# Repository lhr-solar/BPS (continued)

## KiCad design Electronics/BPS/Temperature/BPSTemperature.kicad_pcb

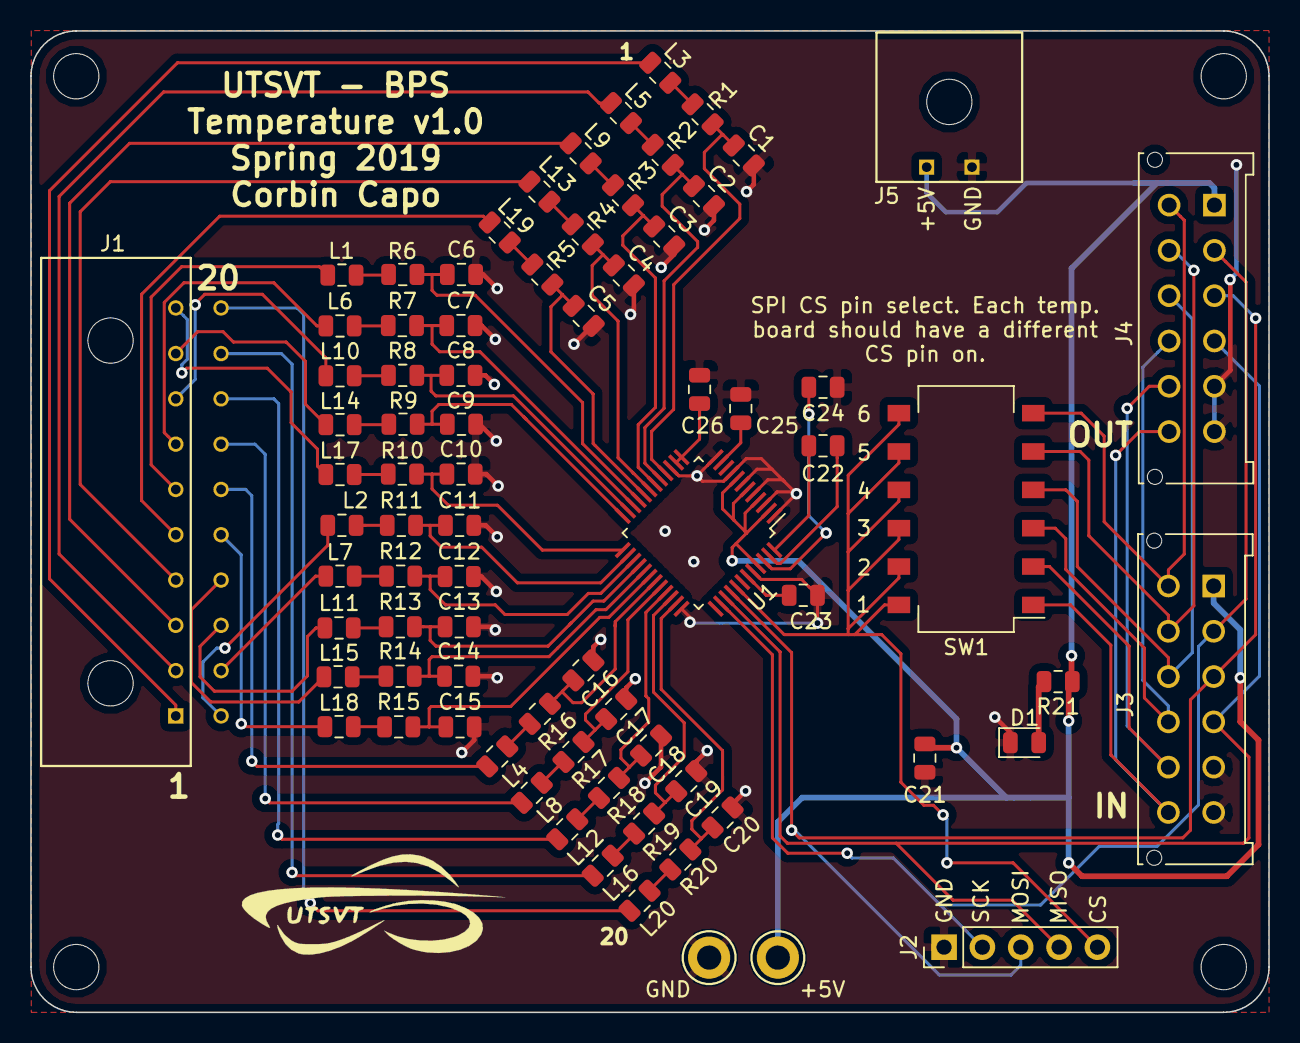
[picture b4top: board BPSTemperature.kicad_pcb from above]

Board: 2 copper layers, 82.0 x 65.0 mm, 81 parts (0 on the bottom side), 79 nets.

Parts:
+5V: TestPoint; TestPoint_Keystone_5005-5009_Compact
C1, C2, C3, C4, C5, C6, C7, C8, C9, C10, C11, C12, C13, C14, C15, C16, C17, C18, C19, C20, C25, C26: 1uF; C_0805_2012Metric
C21: 0.1uF; C_0805_2012Metric
C22, C23, C24: 10uF; C_0805_2012Metric
D1: LED; LED_0805_2012Metric
GND: TestPoint; TestPoint_Keystone_5005-5009_Compact
J1: Conn_02x10_Counter_Clockwise; 02x10_Microfit_3.0_horizontal
J2: Logic Analyzer; PinHeader_1x05_P2.54mm_Vertical
J3, J4: Conn_02x06_Counter_Clockwise; Molex_MicroFit3.0_2x6xP3.00mm_PolarizingPeg_Vertical
J5: Conn_01x02; 43650-0202_01x02_Microfit 3.0_horizontal
L1, L2, L3, L4, L5, L6, L7, L8, L9, L10, L11, L12, L13, L14, L15, L16, L17, L18, L19, L20: Ferrite_Bead; L_0805_2012Metric
MH1, MH2, MH3, MH4: MountingHole; MountingHole_3mm
R1, R2, R3, R4, R5, R6, R7, R8, R9, R10, R11, R12, R13, R14, R15, R16, R17, R18, R19, R20: 1k; R_0805_2012Metric
R21: 1.55k; R_0805_2012Metric
SW1: SW_DIP_x06; SW_DIP_SPSTx06_Slide_Omron_A6S-610x_W8.9mm_P2.54mm
U1: LTC2983; LQFP-48_7x7mm_P0.5mm

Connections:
+5V: +5V.1, C21.2, J3.1, J4.1, J5.1, R21.1, U1.2, U1.4, U1.6, U1.8, U1.45
/CH1_LPF: J1.1, L3.2
/CH2_LPF: J1.2, L5.2
/CH3_LPF: J1.3, L9.2
/CH4_LPF: J1.4, L13.2
/CH5_LPF: J1.5, L19.2
/CH6_LPF: J1.6, L1.1
/CH7_LPF: J1.7, L6.1
/CH8_LPF: J1.8, L10.1
/CH9_LPF: J1.9, L14.1
/CH10_LPF: J1.10, L17.2
/CH11_LPF: J1.11, L2.1
/CH12_LPF: J1.12, L7.1
/CH13_LPF: J1.13, L11.1
/CH14_LPF: J1.14, L15.1
/CH15_LPF: J1.15, L18.1
/CH16_LPF: J1.16, L4.1
/CH17_LPF: J1.17, L8.1
/CH18_LPF: J1.18, L12.1
/CH19_LPF: J1.19, L16.1
/CH20_LPF: J1.20, L20.1
/CS1: J3.12, J4.12, SW1.1
/CS1_OUT: J2.5, SW1.7, SW1.8, SW1.9, SW1.10, SW1.11, SW1.12, U1.41
/CS2: J3.11, J4.11, SW1.2
/CS3: J3.10, J4.10, SW1.3
/CS4: J3.9, J4.9, SW1.4
/CS5: J3.8, J4.8, SW1.5
/CS6: J3.7, J4.7, SW1.6
/MISO: J2.4, J3.4, J4.4, U1.39
/MOSI: J2.3, J3.3, J4.3, U1.40
/SCK: J2.2, J3.2, J4.2, U1.38
GND: C1.2, C2.2, C3.2, C4.2, C5.2, C6.2, C7.2, C8.2, C9.2, C10.2, C11.2, C12.2, C13.2, C14.2, C15.2, C16.2, C17.2, C18.2, C19.2, C20.2, C21.1, C23.2, C24.2, C25.2, C26.2, D1.1, GND.1, J2.1, J3.5, J3.6, J4.5, J4.6, J5.2, U1.1, U1.3, U1.5, U1.7, U1.9, U1.12, U1.15, U1.36, U1.44
unnamed: C1.1, R1.2, U1.16
unnamed: C2.1, R2.2, U1.17
unnamed: C3.1, R3.2, U1.18
unnamed: C4.1, R4.2, U1.19
unnamed: C5.1, R5.2, U1.20
unnamed: C6.1, R6.2, U1.21
unnamed: C7.1, R7.2, U1.22
unnamed: C8.1, R8.2, U1.23
unnamed: C9.1, R9.2, U1.24
unnamed: C10.1, R10.2, U1.25
unnamed: C11.1, R11.2, U1.26
unnamed: C12.1, R12.2, U1.27
unnamed: C13.1, R13.2, U1.28
unnamed: C14.1, R14.2, U1.29
unnamed: C15.1, R15.2, U1.30
unnamed: C16.1, R16.2, U1.31
unnamed: C17.1, R17.2, U1.32
unnamed: C18.1, R18.2, U1.33
unnamed: C19.1, R19.2, U1.34
unnamed: C20.1, R20.2, U1.35
unnamed: C22.1, U1.48
unnamed: C22.2, U1.47
unnamed: C23.1, U1.43
unnamed: C24.1, U1.46
unnamed: C25.1, U1.11
unnamed: C26.1, U1.13, U1.14
unnamed: D1.2, R21.2
unnamed: L1.2, R6.1
unnamed: L2.2, R11.1
unnamed: L3.1, R1.1
unnamed: L4.2, R16.1
unnamed: L5.1, R2.1
unnamed: L6.2, R7.1
unnamed: L7.2, R12.1
unnamed: L8.2, R17.1
unnamed: L9.1, R3.1
unnamed: L10.2, R8.1
unnamed: L11.2, R13.1
unnamed: L12.2, R18.1
unnamed: L13.1, R4.1
unnamed: L14.2, R9.1
unnamed: L15.2, R14.1
unnamed: L16.2, R19.1
unnamed: L17.1, R10.1
unnamed: L18.2, R15.1
unnamed: L19.1, R5.1
unnamed: L20.2, R20.1

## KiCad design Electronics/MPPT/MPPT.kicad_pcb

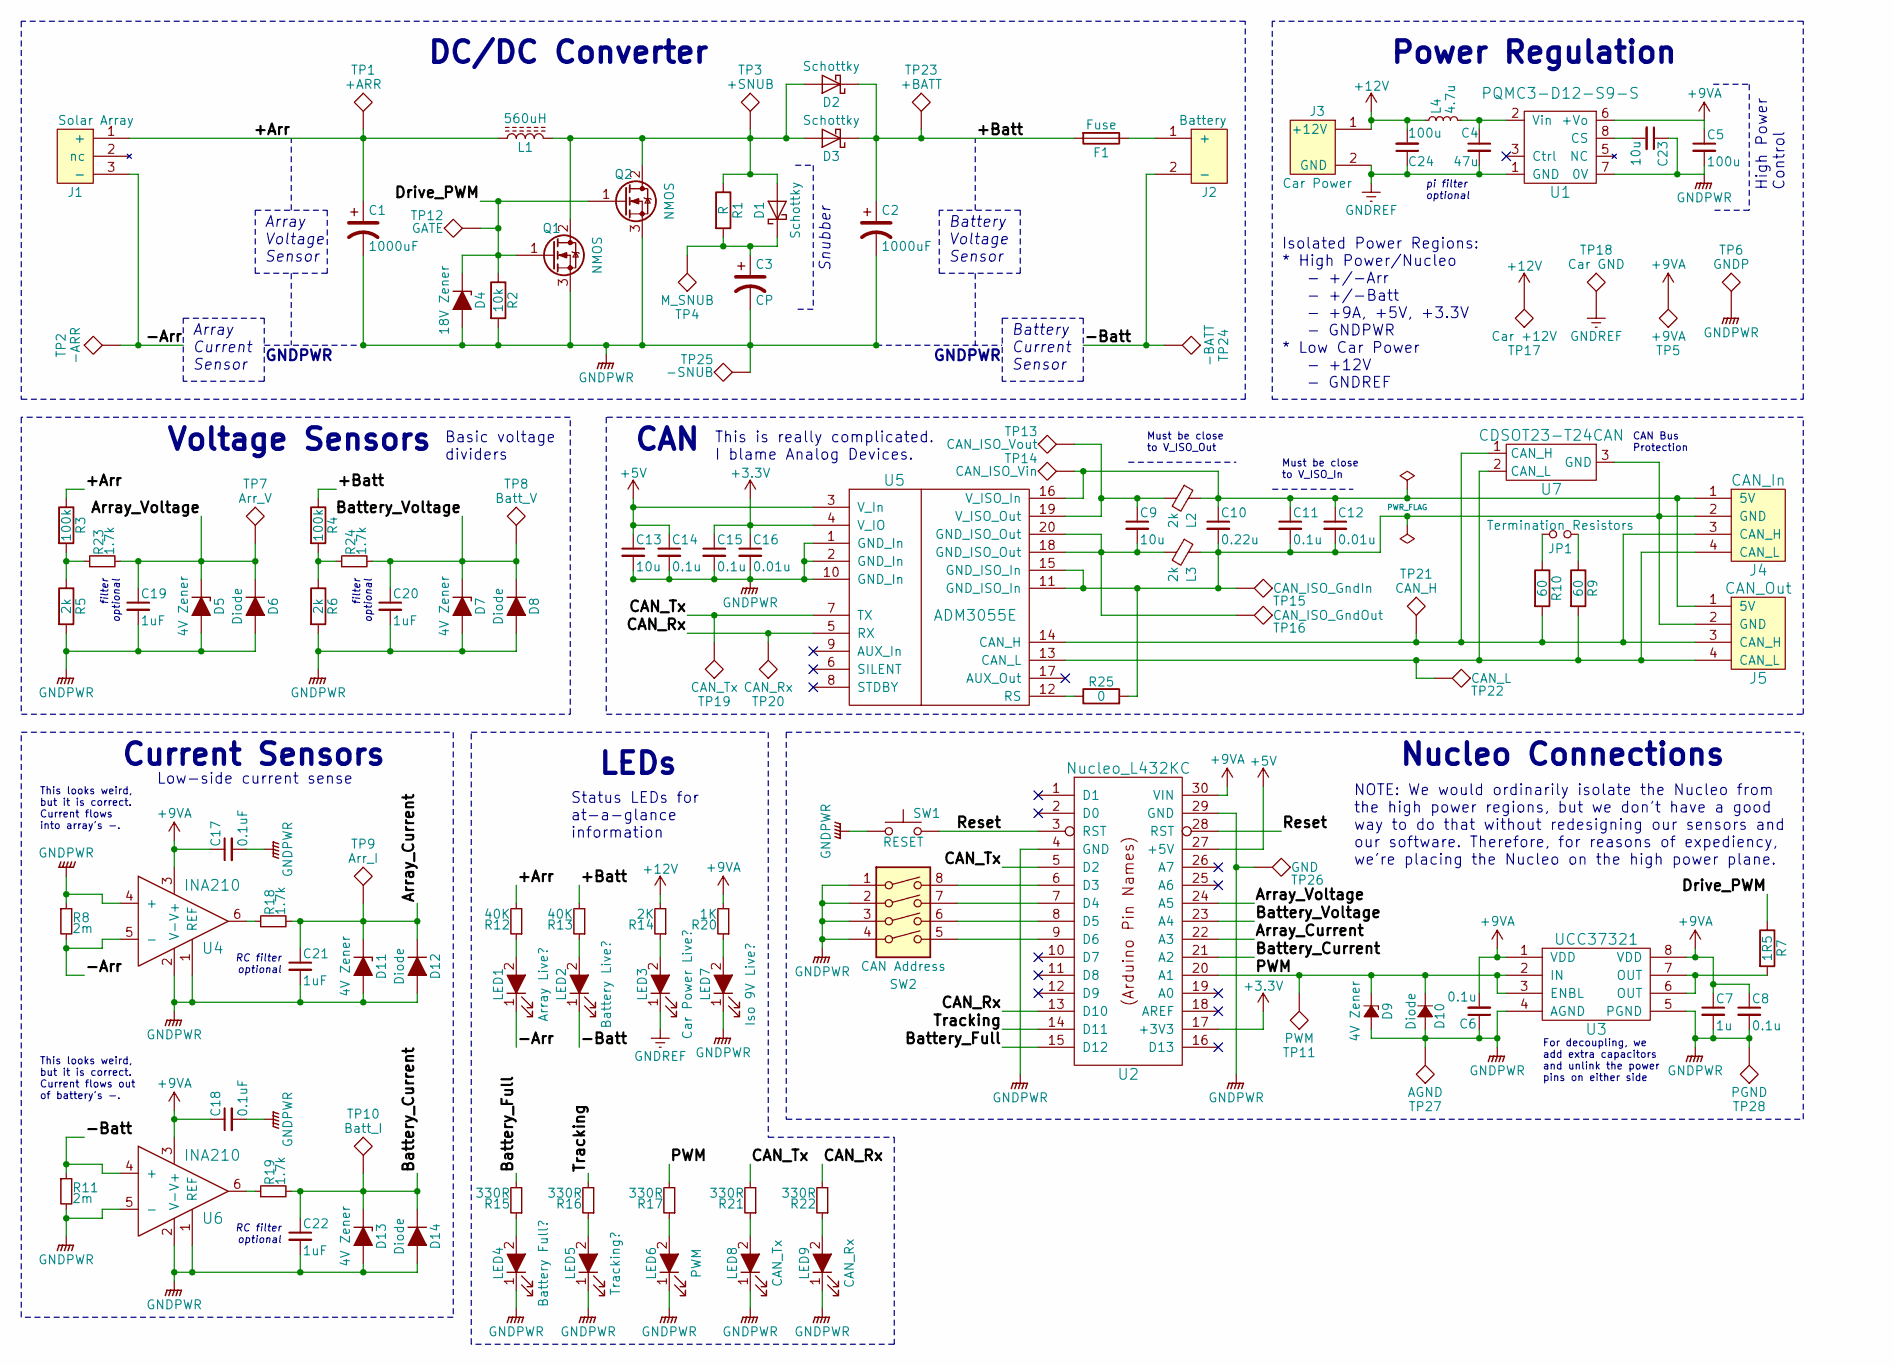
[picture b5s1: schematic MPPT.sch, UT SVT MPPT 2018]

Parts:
C1, C2: 1000uF; CP_Radial_D31mm_P9mm
C3: CP; C_Rect_L26.5mm_W17.0mm_P22.50mm_MKS4
C4: 47u; C_0805_HandSoldering
C5, C24: 100u; C_0805_HandSoldering
C6, C8, C11: 0.1u; C_0805_HandSoldering
C7: 1u; CP_Radial_D10.0mm_P5.00mm
C9, C23: 10u; C_0805_HandSoldering
C10: 0.22u; C_0805_HandSoldering
C12: 0.01u; C_0805_HandSoldering
C13: 10u; C_0805
C14, C15: 0.1u; C_0805
C16: 0.01u; C_0805
C17, C18: 0.1uF; C_0805_HandSoldering
C19, C20, C21, C22: 1uF; C_0805_HandSoldering
D1, D2, D3: Schottky; TO-220-2_Vertical
D4: 18V Zener; D_SMA_Handsoldering
D5, D7, D9, D11, D13: 4V Zener; D_SOD-123F
D6, D8, D10, D12, D14: Diode; D_SOD-123
F1: Fuse; LittelFuse_OMNIBLOK_520Series_PCB
J1: Solar Array; PhoenixContact_PowerCombicon5_GF_3x7.62mm
J2: Battery; PhoenixContact_PowerCombicon5_GF_2x7.62mm
J3: Car Power; Molex_MicroFit3.0_1x2xP3.00mm_PolarizingPeg_Vertical
J4: CAN_In; Molex_MicroFit3.0_1x4xP3.00mm_PolarizingPeg_Vertical
J5: CAN_Out; Molex_MicroFit3.0_1x4xP3.00mm_PolarizingPeg_Vertical
JP1: Termination Resistors; Pin_Header_Straight_1x02_Pitch2.54mm
L1: 560uH; L_Toroid_Vertical_L46.0mm_W19.1mm_P21.80mm_Bourns_5700
L2, L3: 2k; L_0805_HandSoldering
L4: 4.7u; L_0805_HandSoldering
LED1: Array Live?; LED_0805_HandSoldering
LED2: Battery Live?; LED_0805_HandSoldering
LED3: Car Power Live?; LED_0805_HandSoldering
LED4: Battery Full?; LED_0805_HandSoldering
LED5: Tracking?; LED_0805_HandSoldering
LED6: PWM; LED_0805_HandSoldering
LED7: Iso 9V Live?; LED_0805_HandSoldering
LED8: CAN_Tx; LED_0805_HandSoldering
LED9: CAN_Rx; LED_0805_HandSoldering
Q1, Q2: NMOS; TO-247_TO-3P_Vertical
R1: R; R_Axial_Power_L20.0mm_W6.4mm_P22.40mm
R2: 10k; R_1206_HandSoldering
R3, R4: 100k; R_1206_HandSoldering
R5, R6: 2k; R_1206_HandSoldering
R7: 1R5; R_1206_HandSoldering
R8, R11: 2m; R_2512_HandSoldering
R9, R10: 60; R_0805_HandSoldering
R12, R13: 40K; R_1206_HandSoldering
R14: 2K; R_0805_HandSoldering
R15, R16, R17, R21, R22: 330R; R_0805_HandSoldering
R18, R19, R23, R24: 1.7k; R_0805_HandSoldering
R20: 1K; R_0805_HandSoldering
R25: 0; R_0805_HandSoldering
SW1: RESET; SW_PUSH_6mm
SW2: CAN Address; SW_DIP_x4_W7.62mm_Slide_LowProfile
TP1: +ARR; Test_Point_Keystone_5005-5009_Compact
TP2: -ARR; Test_Point_Keystone_5005-5009_Compact
TP3: +SNUB; Test_Point_Keystone_5005-5009_Compact
TP4: M_SNUB; Test_Point_Keystone_5005-5009_Compact
TP5: +9VA; Test_Point_Keystone_5005-5009_Compact
TP6: GNDP; Test_Point_Keystone_5005-5009_Compact
TP7: Arr_V; Test_Point_Keystone_5005-5009_Compact
TP8: Batt_V; Test_Point_Keystone_5005-5009_Compact
TP9: Arr_I; Test_Point_Keystone_5005-5009_Compact
TP10: Batt_I; Test_Point_Keystone_5005-5009_Compact
TP11: PWM; Test_Point_Keystone_5005-5009_Compact
TP12: GATE; Test_Point_Keystone_5005-5009_Compact
TP13: CAN_ISO_Vout; Test_Point_Keystone_5005-5009_Compact
TP14: CAN_ISO_Vin; Test_Point_Keystone_5005-5009_Compact
TP15: CAN_ISO_GndIn; Test_Point_Keystone_5005-5009_Compact
TP16: CAN_ISO_GndOut; Test_Point_Keystone_5005-5009_Compact
TP17: Car +12V; Test_Point_Keystone_5005-5009_Compact
TP18: Car GND; Test_Point_Keystone_5005-5009_Compact
TP19: CAN_Tx; Test_Point_Keystone_5005-5009_Compact
TP20: CAN_Rx; Test_Point_Keystone_5005-5009_Compact
TP21: CAN_H; Test_Point_Keystone_5005-5009_Compact
TP22: CAN_L; Test_Point_Keystone_5005-5009_Compact
TP23: +BATT; Test_Point_Keystone_5005-5009_Compact
TP24: -BATT; Test_Point_Keystone_5005-5009_Compact
TP25: -SNUB; Test_Point_Keystone_5005-5009_Compact
TP26: GND; Test_Point_Keystone_5005-5009_Compact
TP27: AGND; Test_Point_Keystone_5005-5009_Compact
TP28: PGND; Test_Point_Keystone_5005-5009_Compact
U1: PQMC3-D12-S9-S; CUI_PQMC3-S
U2: Nucleo_L432KC; NucleoL432KC
U3: UCC37321; SOIC-8_4.00x5.00mm_Pitch1.27mm
U4, U6: INA210; SOIC-6_1.40x2.15mm_Pitch0.65mm
U5: ADM3055E; SOIC-20W_7.5x15.4mm_Pitch1.27mm
U7: CDSOT23-T24CAN; SOT-23W_Handsoldering

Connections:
+3V3: C15.1, C16.1, U2.17 (+3V3), U5.4 (V_IO)
+5V: C13.1, C14.1, U2.27 (+5V), U5.3 (V_In)
+9VA: C5.1, C6.2, C7.1, C8.1, C17.1, C18.1, R20.2, TP5.1, U1.6 (+Vo), U2.30 (VIN), U3.1 (VDD), U3.8 (VDD), U4.3 (V+), U6.3 (V+)
/+Arr: C1.1, J1.1 (+), L1.1, R3.1, R12.2, TP1.1
/+Batt: C2.1, D2.1 (K), D3.1 (K), F1.2, R4.1, R13.2, TP23.1
/-Arr: J1.3 (-), LED1.1 (K), R8.2, TP2.1, U4.5 (-)
/-Batt: J2.2 (-), LED2.1 (K), R11.1, TP24.1, U6.4 (+)
/Array_Current: C21.1, D11.1 (K), D12.1 (K), R18.2, TP9.1, U2.22 (A3)
/Array_Voltage: C19.1, D5.1 (K), D6.1 (K), R23.2, TP7.1, U2.24 (A5)
/Battery_Current: C22.1, D13.1 (K), D14.1 (K), R19.2, TP10.1, U2.21 (A2)
/Battery_Full: R15.2, U2.15 (D12)
/Battery_Voltage: C20.1, D7.1 (K), D8.1 (K), R24.2, TP8.1, U2.23 (A4)
/CAN_Rx: R22.2, TP20.1, U2.13 (D10), U5.5 (RX)
/CAN_Tx: R21.2, TP19.1, U2.5 (D2), U5.7 (TX)
/Drive_PWM: D4.1 (K), Q1.1 (G), Q2.1 (G), R2.1, R7.1, TP12.1
/PWM: D9.1 (K), D10.1 (K), R17.2, TP11.1, U2.20 (A1), U3.2 (IN), U3.3 (ENBL)
/Reset: SW1.2, U2.3 (RST), U2.28 (RST)
/Tracking: R16.2, U2.14 (D11)
GNDPWR: C1.2, C2.2, C3.2, C5.2, C6.1, C7.2, C8.2, C13.2, C14.2, C15.2, C16.2, C17.2, C18.2, C19.2, C20.2, C21.2, C22.2, C23.1, D4.2 (A), D5.2 (A), D6.2 (A), D7.2 (A), D8.2 (A), D9.2 (A), D10.2 (A), D11.2 (A), D12.2 (A), D13.2 (A), D14.2 (A), LED4.1 (K), LED5.1 (K), LED6.1 (K), LED7.1 (K), LED8.1 (K), LED9.1 (K), Q1.3 (S), Q2.3 (S), R2.2, R5.2, R6.2, R8.1, R11.2, SW1.1, SW2.1, SW2.2, SW2.3, SW2.4, TP6.1, TP25.1, TP26.1, TP27.1, TP28.1, U1.7 (0V), U2.4 (GND), U2.29 (GND), U3.4 (AGND), U3.5 (PGND), U4.1 (REF), U4.2 (V-), U4.4 (+), U5.1 (GND_In), U5.2 (GND_In), U5.10 (GND_In), U6.1 (REF), U6.2 (V-), U6.5 (-)
unnamed: C3.1, D1.1 (K), R1.2, TP4.1
unnamed: C4.1, L4.2, U1.2 (Vin)
unnamed: C9.1, L2.2, TP13.1, U5.19 (V_ISO_Out)
unnamed: C9.2, L3.2, TP16.1, U5.18 (GND_ISO_Out), U5.20 (GND_ISO_Out)
unnamed: C10.1, C11.1, C12.1, J4.1 (5V), J5.1 (5V), L2.1, TP14.1, U5.16 (V_ISO_In)
unnamed: C10.2, C11.2, C12.2, J4.2 (GND), J5.2 (GND), L3.1, R25.2, TP15.1, U5.11 (GND_ISO_In), U5.15 (GND_ISO_In), U7.3 (GND)
unnamed: C23.2, U1.8 (CS)
unnamed: D1.2 (A), D2.2 (A), D3.2 (A), L1.2, Q1.2 (D), Q2.2 (D), R1.1, TP3.1
unnamed: F1.1, J2.1 (+)
unnamed: J4.3 (CAN_H), J5.3 (CAN_H), R10.2, TP21.1, U5.14 (CAN_H), U7.1 (CAN_H)
unnamed: J4.4 (CAN_L), J5.4 (CAN_L), R9.2, TP22.1, U5.13 (CAN_L), U7.2 (CAN_L)
unnamed: JP1.1, R9.1
unnamed: JP1.2, R10.1
unnamed: LED1.2 (A), R12.1
unnamed: LED2.2 (A), R13.1
unnamed: LED3.2 (A), R14.1
unnamed: LED4.2 (A), R15.1
unnamed: LED5.2 (A), R16.1
unnamed: LED6.2 (A), R17.1
unnamed: LED7.2 (A), R20.1
unnamed: LED8.2 (A), R21.1
unnamed: LED9.2 (A), R22.1
unnamed: R7.2, U3.6 (OUT), U3.7 (OUT)
unnamed: R18.1, U4.6
unnamed: R19.1, U6.6
unnamed: R3.2, R5.1, R23.1
unnamed: R4.2, R6.1, R24.1
unnamed: R25.1, U5.12 (RS)
unnamed: SW2.5, U2.9 (D6)
unnamed: SW2.6, U2.8 (D5)
unnamed: SW2.7, U2.7 (D4)
unnamed: SW2.8, U2.6 (D3)

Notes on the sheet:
DC/DC Converter
Current Sensors
Voltage Sensors
Power Regulation
Nucleo Connections
Array Current Sensor
Array Voltage Sensor
Snubber
Battery Current Sensor
Battery Voltage Sensor
Isolated Power Regions: * High Power/Nucleo - +/-Arr - +/-Batt - +9A, +5V, +3.3V - GNDPWR * Low Car Power - +12V - GNDREF
High Power Control
GNDPWR
This looks weird, but it is correct. Current flows into array's -.
This looks weird, but it is correct. Current flows out of battery's -.
Basic voltage dividers
Low-side current sense
NOTE: We would ordinarily isolate the Nucleo from the high power regions, but we don't have a good way to do that without redesigning our sensors and our software. Therefore, for reasons of expediency, we're placing the Nucleo on the high power plane.
CAN
This is really complicated. I blame Analog Devices.
Must be close to V_ISO_Out
Must be close to V_ISO_In
For decoupling, we add extra capacitors and unlink the power pins on either side
LEDs
Status LEDs for at-a-glance information
RC filter optional
CAN Bus Protection
filter optional
pi filter optional

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
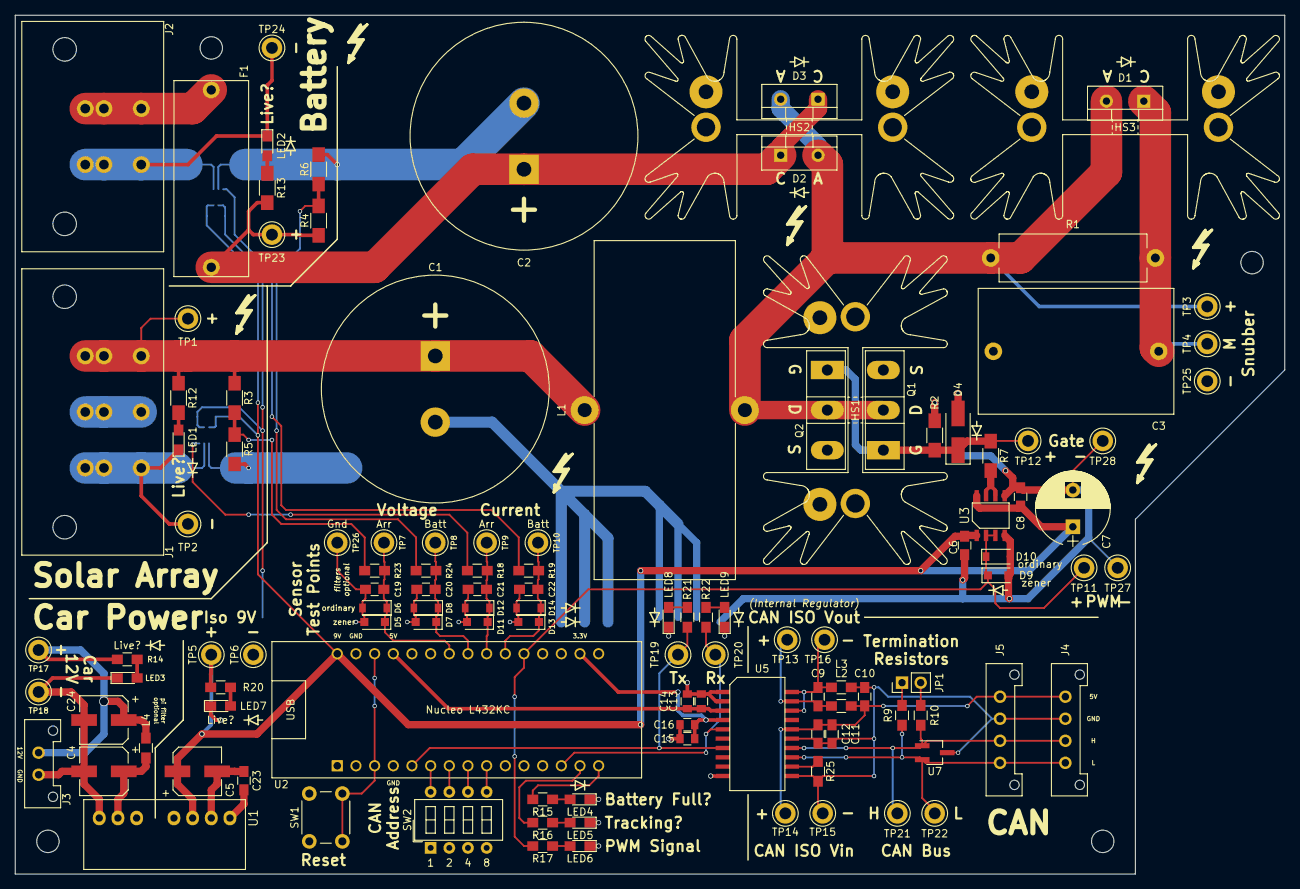
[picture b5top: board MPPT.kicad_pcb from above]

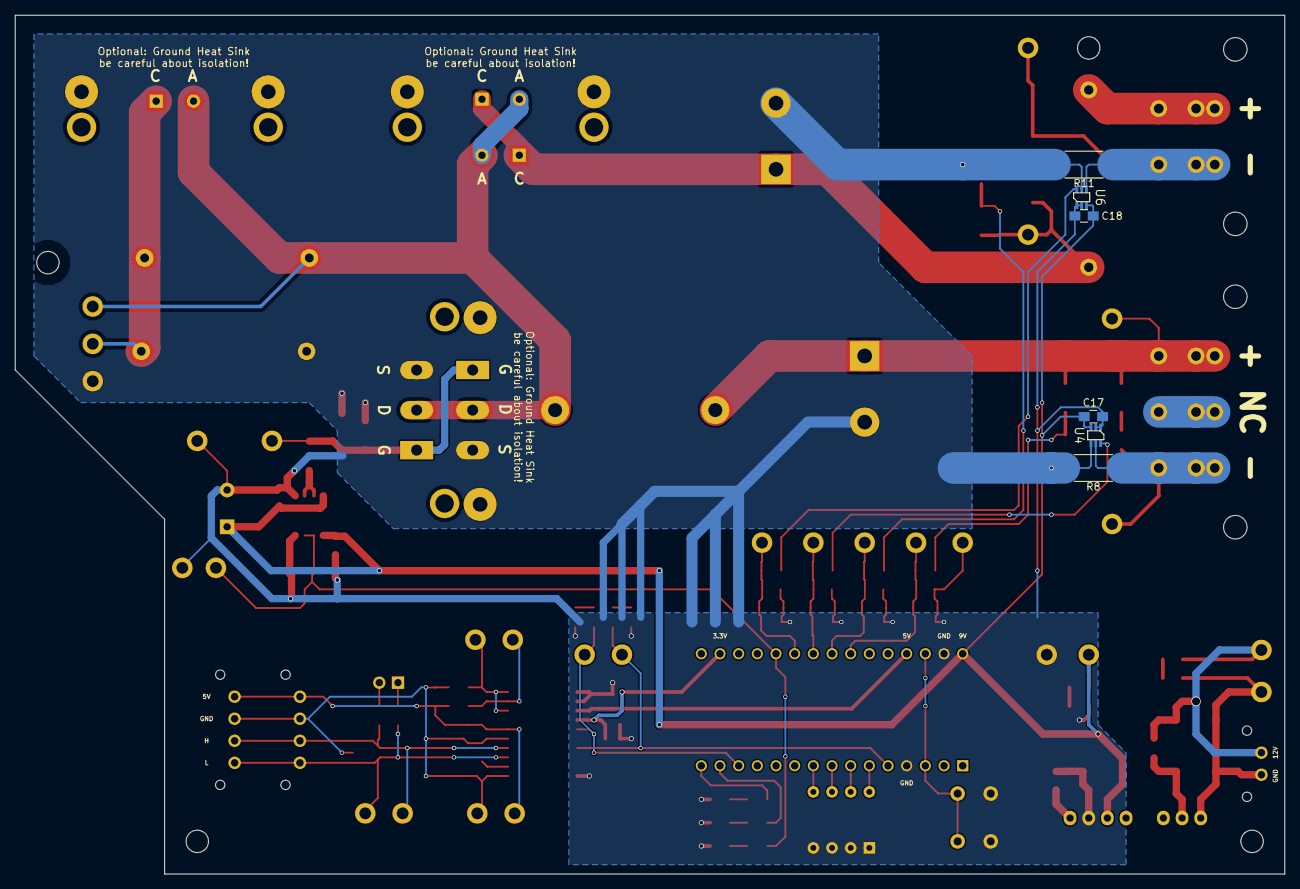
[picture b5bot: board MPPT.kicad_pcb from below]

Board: 2 copper layers, 172.7 x 116.8 mm, 125 parts (6 on the bottom side), 53 nets.

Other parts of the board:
HS1, HS2, HS3: Heatsink_Fischer_SK129-STS_42x25mm_2xDrill2.5mm

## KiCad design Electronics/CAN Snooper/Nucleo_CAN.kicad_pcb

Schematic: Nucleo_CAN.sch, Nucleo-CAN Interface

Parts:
C1: 2.2u; C_0805_HandSoldering
C2: 4.7u; C_0805_HandSoldering
C3, C4, C5, C6: 0.1u; C_0805_HandSoldering
D1: 12V Iso Power; LED_0805_HandSoldering
D2: 5V Iso Power; LED_0805_HandSoldering
D3: 9V Power; LED_0805_HandSoldering
D4: 3.3V Power; LED_0805_HandSoldering
J1: CAN_In; Molex-MiniFitJr-4-peg
J2: CAN_Out; Molex-MiniFitJr-4-peg
JP1: CAN Resistors; SL-102-X-XX_1x02
R1: 1k; R_0805_HandSoldering
R2: 330; R_0805_HandSoldering
R3: 510; R_0805_HandSoldering
R4: 160; R_0805_HandSoldering
R5, R6: 60; R_0805_HandSoldering
SW1: Reset; SW_PUSH_6mm
T1: 12V Iso Test; Measurement_Point_2_Round-SMD-Pad_Small
T2: 5V Iso Test; Measurement_Point_2_Round-SMD-Pad_Small
T3: 9V Test; Measurement_Point_2_Round-SMD-Pad_Small
T4: 3.3V Test; Measurement_Point_2_Round-SMD-Pad_Small
T5: CAN PwrSense Test; Measurement_Point_Round-SMD-Pad_Small
T6: CAN Tx Test; Measurement_Point_Round-SMD-Pad_Small
T7: CAN Rx Test; Measurement_Point_Round-SMD-Pad_Small
T8: CAN Input GND Test; Measurement_Point_Round-SMD-Pad_Small
T9: CAN H Test; Measurement_Point_Round-SMD-Pad_Small
T10: CAN L Test; Measurement_Point_Round-SMD-Pad_Small
T11: CAN Output GND Test; Measurement_Point_Round-SMD-Pad_Small
U1: PDS1-S12-S9-M; PDS1-M
U2: MCP1702T-5002E/CB; SOT-23W
U3: Nucleo_L432KC; NucleoL432KC
U4: ADM3054; SOIC-16W_7.5x10.3mm_Pitch1.27mm

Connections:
+3V3: C5.1, R4.1, T4.1, U3.17 (+3V3), U4.7 (Vdd1)
+5VP: C4.1, C6.1, R2.1, T2.1, U2.3 (VO), U4.13 (Vdd2)
+9V: C2.1, R3.1, T3.1, U1.5 (Vo), U3.30 (VIN)
+12V: C1.1, C3.1, J1.1, J2.1, R1.1, T1.1, U1.2 (Vin), U2.1 (VI)
/CAN_H: J1.3, J2.3, R5.1, T9.1, U4.12 (CANH)
/CAN_L: J1.4, J2.4, R6.1, T10.1, U4.11 (CANL)
/CAN_PwrSense: T5.1, U3.9 (D6), U4.4 (Vd2s)
/CAN_Rx: T7.1, U3.13 (D10), U4.5 (Rxd)
/CAN_Tx: T6.1, U3.5 (D2), U4.6 (Txd)
/RST: SW1.1, U3.3 (RST), U3.28 (RST)
GND: C2.2, C5.2, D3.1 (K), D4.1 (K), SW1.2, T3.2, T4.2, T8.1, U1.4 (GNDo), U3.4 (GND), U3.29 (GND), U4.2 (GND1), U4.3 (GND1), U4.8 (GND1)
GNDPWR: C1.2, C3.2, C4.2, C6.2, D1.1 (K), D2.1 (K), J1.2, J2.2, T1.2, T2.2, T11.1, U1.1 (GNDi), U2.2 (GND), U4.9 (GND2), U4.16 (GND2)
unnamed: D1.2 (A), R1.2
unnamed: D2.2 (A), R2.2
unnamed: D3.2 (A), R3.2
unnamed: D4.2 (A), R4.2
unnamed: JP1.1, R5.2
unnamed: JP1.2, R6.2

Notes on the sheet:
Power LEDs, Test Points
Power
Nucleo Power
CAN Power
(Isolated from CAN)
CAN Interface
Nucleo Board
CAN + PWR Connection

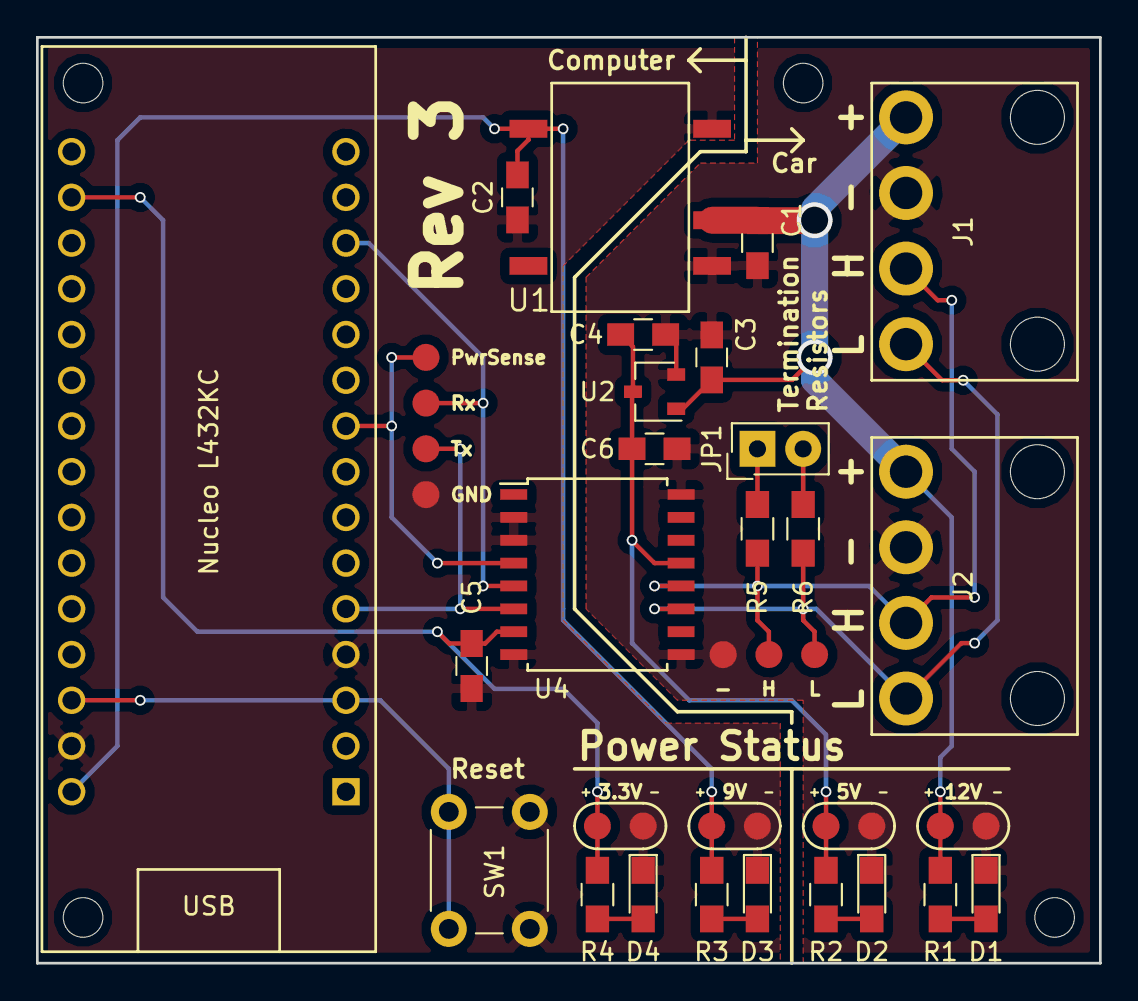
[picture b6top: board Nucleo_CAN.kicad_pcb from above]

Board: 2 copper layers, 59.1 x 51.4 mm, 35 parts (0 on the bottom side), 18 nets.

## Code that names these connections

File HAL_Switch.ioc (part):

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Mcu.Name=STM32F413R(G-H)Tx
Mcu.Package=LQFP64
Mcu.UserName=STM32F413RHTx
PA10.Signal=GPIO_Output
PA11.Signal=GPIO_Output
PA12.Signal=GPIO_Output
PA13.Signal=SYS_JTMS-SWDIO
PA14.Signal=SYS_JTCK-SWCLK
PA15.Signal=GPIO_Output
PA2.Mode=Asynchronous
PA2.Signal=USART2_TX
PA3.Mode=Asynchronous
PA3.Signal=USART2_RX
PA4.Signal=GPIO_Output
PA5.Signal=GPIO_Output
PA6.Signal=GPIO_Output
PA7.Signal=GPIO_Output
PA8.Mode=I2C
PA8.Signal=I2C3_SCL
PA9.Signal=GPIO_Output
PB0.Signal=GPIO_Output
PB1.Signal=GPIO_Input
PB10.Mode=Asynchronous
PB10.Signal=USART3_TX
PB12.Signal=GPIO_Output
PB14.Signal=S_TIM12_CH1
PB15.Signal=S_TIM12_CH2
PB3.Mode=Full_Duplex_Master
PB3.Signal=SPI1_SCK
PB4.Mode=Full_Duplex_Master
PB4.Signal=SPI1_MISO
PB5.Mode=Full_Duplex_Master
PB5.Signal=SPI1_MOSI
PB8.Mode=CAN_Activate
PB8.Signal=CAN1_RX
PB9.Mode=CAN_Activate
PB9.Signal=CAN1_TX
PC0.Signal=GPIO_Output
PC1.Signal=GPIO_Output
PC10.Mode=Full_Duplex_Master
PC10.Signal=SPI3_SCK
PC11.Mode=Full_Duplex_Master
PC11.Signal=SPI3_MISO
PC12.Mode=Full_Duplex_Master
PC12.Signal=SPI3_MOSI
PC2.Signal=GPIO_Output
PC3.Signal=GPIO_Output
PC4.Signal=GPIO_Output
PC5.Mode=Asynchronous
PC5.Signal=USART3_RX
PC6.Signal=S_TIM3_CH1
PC7.Signal=S_TIM3_CH2
PC9.Mode=I2C
PC9.Signal=I2C3_SDA
PD2.Signal=GPIO_Output
RCC.SYSCLKFreq_VALUE=16000000
board=custom

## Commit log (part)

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2023-03-19 peep the cursed code
2023-03-20 First Draft
2023-03-20 probably wont work
2023-03-20 minor comments
2023-03-20 good i think
2023-03-20 stuff works on master now
2023-03-20 no more reference
2023-03-20 new errors?
2023-03-20 test file
2023-03-20 build please?
2023-03-20 Proof of Concept
2023-03-20 sending messages fr fr
2023-03-20 commit before rebase
2023-03-20 interim commits, still changes to make
2023-03-20 Code Quality
2023-03-22 fixed fault state sending
2023-03-25 fix redundant function
2023-03-25 change to int 8
2023-03-25 Can fault state (#548)
    * minor comments
    * Built CAN code
    * Added temp can-payload in fault state task
    * always deinit in faultstate
    * use PLL delay
    * fixed fault state sending
2023-03-25 this should fail
2023-03-25 this should not fail
2023-03-25 Debugging changes
2023-03-25 questionable functionality
2023-03-25 dumb change
2023-03-25 Added file
2023-03-25 Voltage testing (#572)
    * Voltages won't update after reading first time
    * Fix whitespace and properly use Minions ASIC Mutex
    * Gave larger FIFO to BSP UART. Removed BSP Toggle from Test File (one race condition). For some reason Mions.cells.c_codes is not updating during operation. Need to figure out why.
    * Updated files to show more information during compile time. Also changed usage of MinionsAsic Mutex in Temperature.c
    This reverts commit 62d020e48e5f709fda7147cb3a435738f966ad75.
    * bsp pll delay um 🙄
2023-03-25 I forgot NVIC
2023-03-25 Voltage testing (#572)
    * Voltages won't update after reading first time
    * Fix whitespace and properly use Minions ASIC Mutex
    * Gave larger FIFO to BSP UART. Removed BSP Toggle from Test File (one race condition). For some reason Mions.cells.c_codes is not updating during operation. Need to figure out why.
    * Updated files to show more information during compile time. Also changed usage of MinionsAsic Mutex in Temperature.c
    This reverts commit 62d020e48e5f709fda7147cb3a435738f966ad75.
    * bsp pll delay um 🙄
2023-03-25 maxparallel change in simple-tests
2023-03-25 Autogenerate/autorun Simulator Tests (#518)
    * add charging/discharging overtemp tests
    * first commit of automated testing, needs makefile changes and implementation
    * makefile can now compile testgen
    * make the pretty makefile colors work right
    * Test_Generator now working, addressed raymond bugs
    * makeclean removes autogenerated simulator files
2023-03-25 fault state docs v1 (#562)
2023-03-25 Make tests workflow (#543)
    * Made things easier to debug
    * Fixing all test make issues. Need to make script to run simulator tests
    * Made good script to make all test files
    * Add sudo so workflow works
    * debugging cwd
    * shell env
2023-03-25 moved delay_u and m to BSP_PLL, also renamed with BSP prefix (#566)
    * moved delay_u and m to BSP_PLL, also renamed with BSP prefix
    * fixed reference
    * made loops volatile, added PLL prefix
    * replaced ltc2315
    * Updated Documentation
    ---------
2023-03-25 More Testing
2023-03-25 Added empty function implementations for _fstat_r and _isatty_r (#546)
    * Added empty function implementations for _fstat_r and _isatty_r
    * Updated isatty return value
    * Added comments
    ---------
2023-03-25 SPI Error Handling (#565)
    * propogate errors thru SPI_Write() and SPI_Read()
    * update headers
    * add simulator revisions
    * enter fault state on spi error
    * change from bools to errorstatus
    * update comments
2023-03-25 kill switch for simulator (#545)
    * kill switch for simulator
    * add killswitch test output
    * remove extra func from sim pwm
    * add more states to killswitch test. works on estop properly
    * add killswitch.json to tests
    * Update simple-tests.yml
2023-03-25 Removed code that was used for testing
2023-03-25 Fixed test file
2023-03-25 python is python
2023-03-25 fix test.sh
2023-03-26 Comment
2023-03-28 display every (editable) #define value. can be adjusted to show all config defines if need
2023-03-29 Added stuff for reentry into EnterFaultState and allowing multiple lights to turn on
2023-03-29 white space fix
2023-03-29 indent fix??
2023-03-30 Resolved issue
2023-04-01 math and sign changes
2023-04-01 trying to hunt down transition fixes
2023-04-01 remove rebase
2023-04-01 forgot to save
2023-04-01 Temperature Works
2023-04-01 Removed commented code
2023-04-01 Remove debugging stuff
2023-04-01 Fixed simulator
2023-04-01 fix test build
2023-04-01 this should pass simulator test
2023-04-01 Fix SafetyCheck_Sem4 redefinition error in tests
2023-04-01 actually fixed merge conflict
2023-04-02 Fix whitespace
2023-04-02 added loops,
2023-04-08 4space
2023-04-08 never pushed these
2023-04-08 simulator fails should reach github
2023-04-08 file
2023-04-08 some comments
2023-04-08 testing (do not use)
2023-04-08 :grin: :japanese_goblin: new test file for delayus
2023-04-08 :sad: stuff
2023-04-14 Fixed contactor bug. Changed priorities to start from 1. Fixed UART bug
2023-04-15 Fixed Contactor bug. We have a large cap at input
2023-04-15 Remove EEPROM Functionality
2023-04-15 manual data fail test
2023-04-15 Added Fault Lights Test
2023-04-15 this shoudl fail too, but more advanced
2023-04-15 this will now work
2023-04-15 Removed open drain configuration
2023-04-15 tested delays
2023-04-15 comment fixes
2023-04-15 Fix Simulator Workflow bugs (#576)
    * fix json file length
    * maxparallel change in simple-tests
    * upgrade simulator version
    * fix test build
    * Fix SafetyCheck_Sem4 redefinition error in tests
2023-04-15 update pid loop (#561)
    * change to int 8
    * math and sign changes
2023-04-15 fix build issue
2023-04-15 Voltages are now updated
2023-04-16 Temperature Bug Fixes (#580)
    * Fixed bugs, added printf statements to debug
    * made EnterFaultState Entry nicer
    * changed type of Fault_Bitmap for better error messages
    * Added .swp file type to gitignore (#532)
    * Modified bsp_can_write to return an error if the length of the data is greater than 8 bytes. (#534)
    * Update Debugging info and add PR check (#536)
2023-04-29 rebassey
2023-04-29 lights loop with patterns
2023-04-29 me when simulator 🐒
2023-04-29 grrrr
2023-04-30 BPS Works
2023-05-01 Removed debugging stuff
2023-05-01 BPS Works (#587)
    * BPS Works
    * 😍 hehe poop
    * Removed debugging stuff
2023-06-11 manthan fixes
2023-06-11 fix indentation
2023-06-18 fixed submodule pathing so that github workflow will work
2023-07-28 fix error not being updated
2023-07-28 fix DelayMs being called DelayM
2023-08-26 builds now hehe
2023-08-26 Test
2023-09-19 embedded sharepoint freertos submodule add
2023-09-19 remove embedded sharepoint submodule, freertos needs to manual rn
2023-09-23 freertos swap micrium mutexes and semaphores, need to fix TCBs and tasks in general
2023-09-23 modify tasks to use freertos stuff w regex; may have missed some
2023-09-23 notes to self in rtos config.h
2023-09-30 dummy to test simulator we wooo
2023-09-30 added receive queue and CANBusProducer task to grab from that receive queue, :smile: :penguin:
2023-09-30 fix sim issue
2023-10-07 some changes
2023-10-07 updated mutex buffer
2023-10-07 inshallah it wokrs
2023-10-14 CANProducer working, CAN_Task test can send/receive and print messages
2023-10-14 two can sends one receive :japanese_goblin:
2023-10-21 CAN filtering for only array state change applied, test also updated :boom:
2023-10-21 sending contactor statuses added and Test_CAN_task.c updated with a slower can transmit(more realistic)
2023-11-04 Added CheckArrayContactors test interfacing with Task CheckContactor
2023-11-04 PR changes and fixed functions of Contactor_State test
2023-11-04 the message lenght was wrong...
2023-11-11 pushin
2023-11-11 few logic fixes
2023-11-11 making tests
2023-11-11 fixed retarget
2023-11-11 build
2023-11-11 reverted append
2023-11-11 fixed retarget again
2023-11-11 applied changes from suggestions
2023-11-11 Added link to strobe light
2023-11-13 Added link to strobe light (#594)
2023-11-18 fixed smile?
2023-11-18 now it compiles!! *surprised pikachu face
2023-11-18 Changes + Test
2023-11-18 removed include
2023-11-21 end line
2023-11-25 fix simulator compile bug
2023-11-30 comment fix
2023-12-02 one line
2023-12-02 fix again LMFAOO
2023-12-02 nathan big brain fix
2023-12-02 Updating Docs
2023-12-02 Updating Docs (#596)
2023-12-02 nubers change
2023-12-02 TODO: filter broke
2024-01-20 filter fix
2024-01-27 remove empty returns
2024-01-27 address overflow detect
2024-02-03 update func usages
2024-02-03 save/restoring across power cycles
2024-02-06 Init Battery Balance Task
2024-02-15 fan driver starting
2024-02-15 added time measurements to each task
2024-02-16 Added task
2024-02-16 simulator build fix
2024-02-17 added ecape characters to print
2024-03-02 progress
2024-03-07 usb can mirroring + more build issues + removed having fun in the rules
2024-03-07 output data rate volttemp (#598)
    * a
    * raymond
2024-03-10 fixed skip assignment and scheduler lock error
2024-03-19 added debug mode
2024-03-20 added voltage skip assignment, need to fix open wire
2024-03-21 continued work, need to fix open wire
2024-03-21 started temp skip
2024-03-21 fixed loops
2024-03-21 screw open wire
2024-03-21 Raymond + Tianda changes except for weak variable, want to look into that
2024-03-22 quick makefile fix + voltage fix (all but last minion read properly)
2024-03-22 fixed temp checkstatus
2024-03-22 fixed how chargeCheck reads temperature
2024-03-22 temp is fucked
2024-03-22 added to dos and the changed can temp loop
2024-03-23 Revert "still does not work :("
    This reverts commit 7abdde2e2014043166b4b74eb8bb03d7952b1da2.
2024-03-31 cleanup
2024-03-31 Voltage skip assignment (#601)
    * added debug mode
    * added voltage skip assignment, need to fix open wire
    * woop woop, added some to do
    * continued work, need to fix open wire
    * ready for review except for open_wire
    * screw open wire
2024-04-01 pedantic semantics
2024-04-01 minor formatting for code blocks
2024-04-01 add to readme for how to use DEFINES override (#593)
    * add to readme for how to use DEFINES override
    * minor formatting for code blocks
    ---------
2024-04-01 revert some things
2024-04-01 new print queue framework & calling pattern, new fifo lib
2024-04-06 Wear Leveling Draft
2024-04-06 task sorta works -- some race causing issues with the task.
2024-06-07 minor timeout change
2024-06-07 Buffer print (#589)
    * print queue v0
    * revert some things
    * new print queue framework & calling pattern, new fifo lib
    * task
    * task sorta works -- some race causing issues with the task.
    * works and doesn't get starved!!
2024-06-11 ended up rewriting all of volttemp
2024-06-11 fix build issues? add temperature/voltage range functions
2024-06-11 mostly fixing tests but tests helped me find one bug !!
2024-06-29 Volttemp + Amperes Refactor (#603)
    * ended up rewriting all of volttemp
    * amperes refactor
    * fix build issues? add temperature/voltage range functions
    * mostly fixing tests but tests helped me find one bug !!
    * minor changes to amps trip logic
2024-06-29 docs & cleanup
2024-06-29 improved print -- do raw bytes only + crc
2024-07-10 Mirror CAN traffic over UART/USB (#604)
    * basic printing and parsing functionality
    * improved print -- do raw bytes only + crc
    * revert to basic py example
    * docs & cleanup
    * a
2024-07-10 update sim bsp
2024-07-10 update sim tests
2024-07-11 filtering to amps & try to fix sim tests with filtering
2024-07-11 add temperature reorder buf
2024-07-14 sum fixes
2024-07-15 scroot
2024-07-16 amperes board too noisy. adjust limits to account for poor tolerances.
2024-09-14 made getFanSpeed function
2025-03-03 hacky temp fix
2025-03-03 add mppt status stuff
2025-03-28 tested on hw + 2 arrays
2025-05-12 temp debug
2025-05-13 temp printing
2025-05-14 ignition state
2025-05-14 add new CAN ID to send fault state
2025-05-17 shitties code known to man (now waiting for mppt to be disabled before turning on array Contactor)
2025-05-19 work
2025-06-01 can queue is dead (Crab rave)
2025-06-04 i literally could give less of a shit at this point
2025-06-04 no shot this will work
2025-06-04 First try?????????
2025-06-05 Can Receive Rewrite (#609)
    * blag
    * no shot this will work
    * First try?????????
    * push final v2
2025-06-21 safety verified
2025-07-01 add voltage and tmep counter
2025-11-11 increase u/o volt counter thresh
2025-11-13 nart
2025-11-13 unsafe bps (higher ovolt setpoints to allow more charging)
2025-11-13 undervolt sag
